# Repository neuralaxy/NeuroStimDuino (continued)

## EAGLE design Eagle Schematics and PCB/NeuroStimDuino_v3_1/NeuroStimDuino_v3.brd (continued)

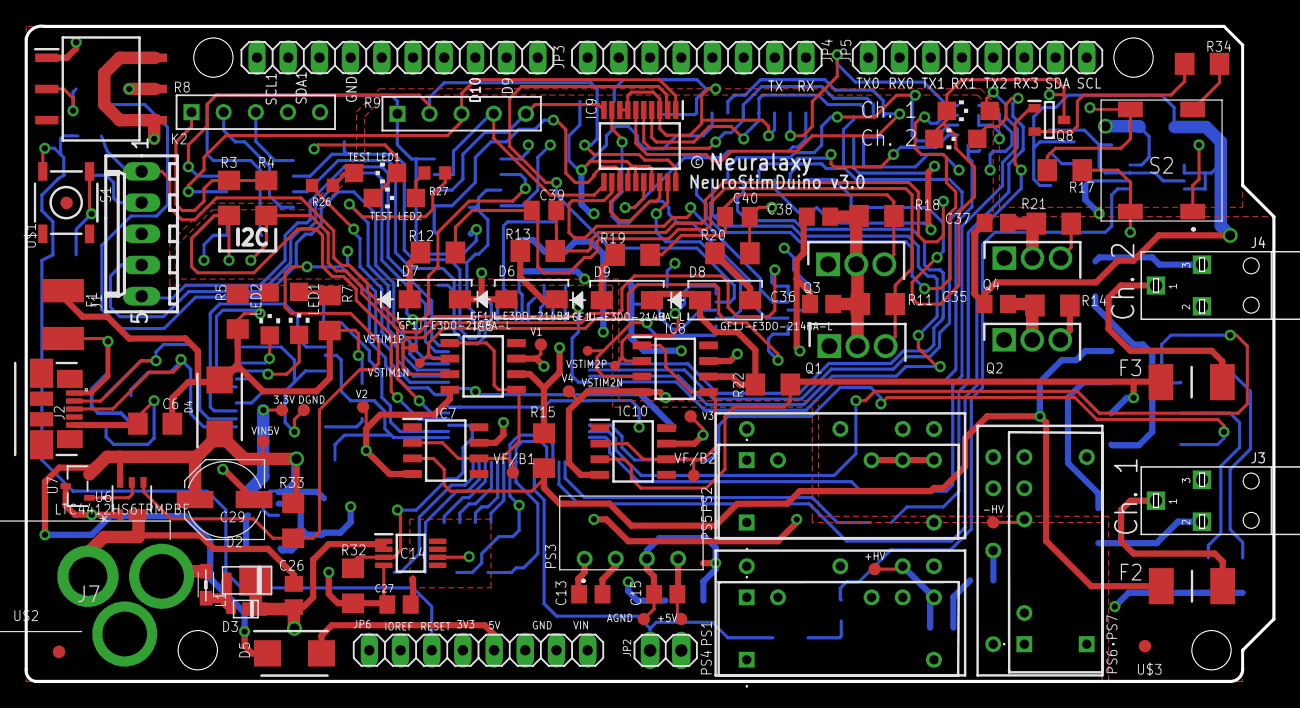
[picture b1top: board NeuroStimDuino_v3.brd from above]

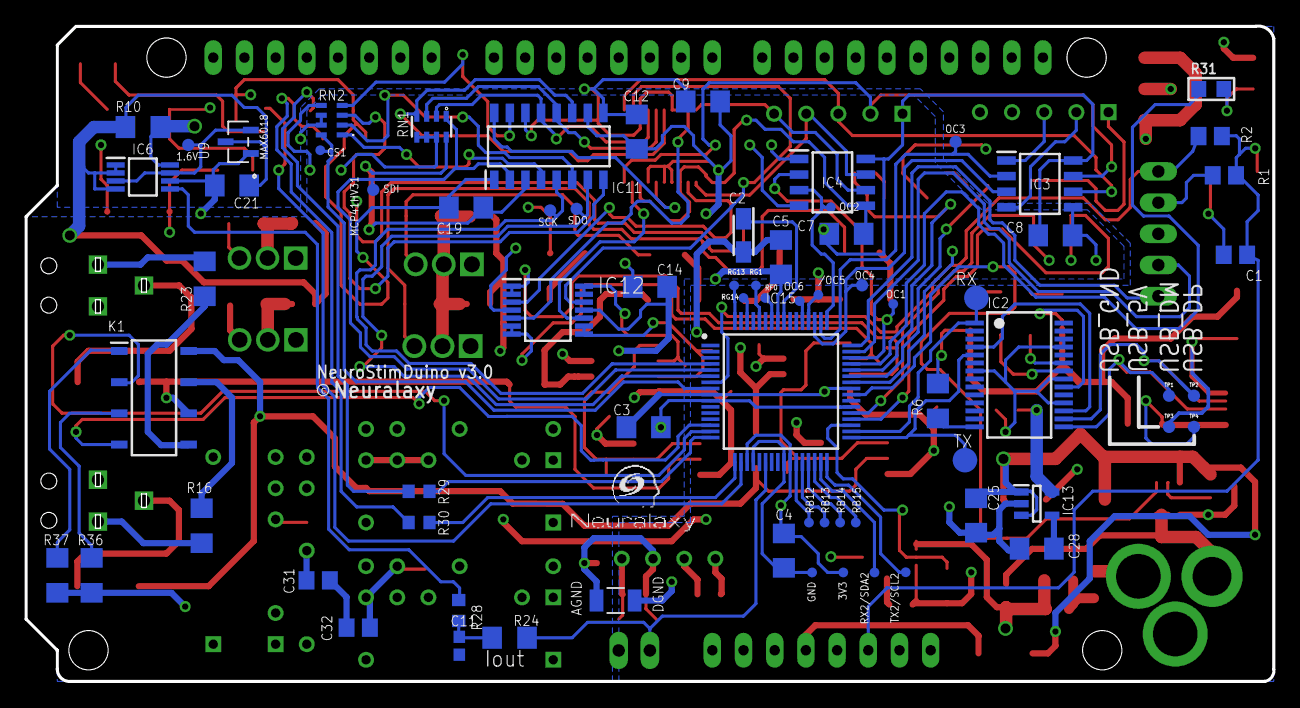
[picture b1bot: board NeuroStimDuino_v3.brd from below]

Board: 4 copper layers, 101.6 x 53.4 mm, 177 parts (68 on the bottom side), 125 nets.

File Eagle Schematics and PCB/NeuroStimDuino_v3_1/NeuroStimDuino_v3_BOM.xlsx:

Qty | Value | Device | Package | Parts | Description | Column1 | _1
3 | 0.1uF | CGA4J2X7R2A104K125AA | C0805K | C1, C39, C40 | CAPACITOR, American symbol
1 | 56nF | C0603C563J4RACTU | CAPC17595_87N_KEM | C11
9 | 1uF | C0805C105K3RACTU | C0805 | C13, C15, C26, C31, C32, C35, C36, C37, C38 | CAPACITOR, American symbol
1 | 4.7uF | F971C475MAAHT3 | CAPPM3216X180N | C2 | Tantalum Capacitors - Solid SMD 16V 4.7uF 20% 1206 ESR=4Ohm AEC-Q200
1 | 10uF | C2012X7S1E106K125AE | C0805 | C27 | CAPACITOR, American symbol
1 | 47uF | 865230445005 | Wurth Electronik | C29 | 47uF
11 | 0.1uF | C1206C104K3RACTU | C1206 | C3, C4, C5, C7, C8, C9, C12, C14, C19, C21, C25 | CAPACITOR, American symbol
2 | 10nF | CGA5H4X7R2J103K115AA | C1206 | C6, C28 | CAPACITOR, American symbol
1 | SS1P3L | 0025_SS1P3L-M3/84A | DO220AAL | D2 | 1A 30V Schottky Barrier Rectifiers -SS1P3L-M3/84A
1 | MSS1P3L-M3/89A | 1653_MSS1P3L-M3/89A | MICROSMP | D3 | Surface Mount Schottky Barrier Rectifiers - Case microSMP
2 | LSM115JE3_TR13 | LSM115JE3_TR13 | DIOM5436X330N | D4, D5 | Schottky Diodes & Rectifiers Schottky
4 | GF1J-E3DO-214BA-L | GF1J-E3DO-214BA-L | DO-214BA-L | D6, D7, D8, D9
2 | 0453.062MR | 0453.062MR | FUSC6127X294N | F2, F3 | Surface Mount Fuses 125VAC 0.062A 5.5ohms 453 NANO2
1 | ACSL-6410-00TE | ACSL-6410-00TE | SOIC127P599X152-16N | IC11 | Broadcom ACSL-6410-00TE DC Input Logic Gate Output Quad Optocoupler, Surface Mo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
1 | MCP6479-E_ST or TS274IPT | MCP6479-E_ST or TS274IPT | SOP65P640X120-14N | IC12 | Operational Amplifiers - Op Amps Quad, 3MHz Op Amp, E Temp
1 | TPS73633DBVR | TPS73633DBVR | SOT95P280X145-5N | IC13 | Single Output LDO, 400mA, Adj.(1.2 to 5.5V), Cap free, Low Noise, Reverse Curre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
1 | MIC3975-5.0YMM-TR | MIC3975-5.0YMM-TR | SOP65P490X109-8N | IC14 | ic
1 | DSPIC33FJ64GS606-I_PT | DSPIC33FJ64GS606-I_PT | QFP50P1200X1200X120-64N | IC15 | Microchip DSPIC33FJ64GS606-I/PT, 16bit PIC Microcontroller, 40MHz, 64 kB Flash,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
2 | HCPL0531 | HCPL0531 | SOIC127P594X363-8N | IC3, IC4 | Optocoupler 2-Ch Transistor 1MBit/s SO8
2 | AD629ARZ-R7 or INA149AID | AD629ARZ-R7 or INA149AID | SOIC127P600X175-8N | IC5, IC8 | Texas Instruments INA149AID, Differential Amplifier 8-Pin SOIC
1 | TSC2012IST | TSC2012IST | SOP65P490X110-8N | IC6 | SP Amp Current Sense Amp Single 5.5V 8-Pin Mini-SO T/R
2 | OPA140AID | OPA140AID | SOIC127P600X175-8N | IC7, IC10 | 11MHz, Single Supply, Low Noise, Precision, Rail-to-Rail Output, JFET Amplifier
1 | MCP4341-103E_ST | MCP4341-103E_ST | SOP65P640X120-20N | IC9 | 7 bit Digital Potentiometers, 10k, SPI
1 | 22-27-2051-05 | 22-27-2051-05 | 6410-05 | J1 | CONNECTOR
2 | Custom Connector | DC_JACK_081BB-2103300 | 081BB-2103300 | J3, J4
1 | CON-SOCJ-2155 | CON-SOCJ-2155 | CONSOCJ2155 | J7 | DC Power Connectors Power Jack/Connector 2.1mm x 5.5mm
1 | Stackable Header - 2 Pin |  | 1X02 | JP2 | Female Gray Connecter strip 2x1 F V h 8,5 p2,54mm
1 | Stackable Header - 10 Pin | https://robu.in/product/10-pin-female-11mm-tall-stackable-he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 | 1X10 | JP3 | Female Gray Connector strip for Arduino 3V3 bases - 10x1 F V h 8,5 p2,54mm
3 | Stackable Header - 8 Pin | https://robu.in/product/8-pin-female-11mm-tall-stackable-hea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 | 1X08 | JP4, JP5, JP6 | Female Gray Connector strip for Arduino 3V3 bases - 8x1 F V h 8,5 p2,54mm
1 | CPC2125N | CPC2125N | SOP254P610X218-8N | K1 | Solid State Relays - PCB Mount Dual SP-NC SS OptoMOS Relay
1 | LCA717S_DC | LCA717S_DC | SOP254P952X470-6N | K2 | Solid State Relays - PCB Mount 1-Form 30V 2000 mA Solid State Relay
1 | BLM21PG300SN1D | BLM21PG300SN1D | 0805 | L1 | BLM21
4 | LED | APTR3216SGC | CHIPLED_1206 | LED5, LED6, LED7, LED8 | LED
2 | IH0524D or IH0524SH | IH0524D or IH0524SH | IH0524D or IH0524SH | PS4, PS6 or PS1, PS7 | Isolated DC/DC Converters DC-DC, 2W, unreg., dual output, SIP, 3kV
1 | TEA_1-0505 | TEA_1-0505 | TEA10505 | PS3 | 1 Watt DC/DC converter, industrial, +/-10% input, unregulated, highly cost effi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
2 | MJE350 | MJE350 | TO229P300X760X1364-3P | Q1, Q3 | Source: Datasheet
2 | MJE340 | MJE340 | TO229P290X760X1320-3P | Q2, Q4 | MJE340, NPN Bipolar Transistor, 0.5 A 300 V HFE:30 V Power, 3-Pin SOT-32
1 | MMBT3906 | MMBT3906 | SOT95P240X120-3N | Q8 | Transistor GP BJT PNP 40V 0.2A SOT23 Fairchild MMBT3906 PNP Bipolar Transistor,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
1 | 10K | RC0805FR-0710KL | R0805 | R1 | RESISTOR, American symbol
1 | 0.5E | RCWE1206R500FKEA | R1206 | R10 | RESISTOR, American symbol
4 | 35.7K | RT1206FRE0735K7L | R1206 | R11, R14, R18, R21 | RESISTOR, American symbol
4 | 10K, 1/2W | RCS120610K0JNEA | R1206 | R12, R13, R19, R20 | RESISTOR, American symbol
2 | 100E, 1/2W | MCA1206MD1000BP100 | R1206 | R15, R22 | RESISTOR, American symbol
2 | 10E, 3/4W | CRCW120610R0FKEBHP | R1206 | R16, R23 | RESISTOR, American symbol
1 | 3.3K | ERJ-8ENF3301V | R1206 | R17 | RESISTOR, American symbol
1 | 470E | ERJ-8ENF4700V | R0805 | R2 | RESISTOR, American symbol
5 | 330E | ERJ-UP3J331V | R0603 | R26, R27, R28, R29, R30 | RESISTOR, American symbol
2 | 10K | CRGH1206F10K | R1206 | R3, R4 | RESISTOR, American symbol
1 | 100E | R_0805 | R0805 | R31 | RESISTOR
1 | 100K | ERJ-UP8F1003V | R1206 | R32 | RESISTOR, American symbol
1 | 470K | ERJ-UP8F4703V | R1206 | R33 | RESISTOR, American symbol
1 | 220E | ERJ-8ENF2200V | R1206 | R34 | RESISTOR, American symbol
2 | 330E | R-US_R1206 | R1206 | R36, R37 | RESISTOR, American symbol
1 | 4605X-101-221LF | 4605X-101-221LF | BO_4605X | R8
1 | 4605X-101-332LF | 4605X-101-332LF | BO_4605X | R9
1 | CAY16-332J4LF | CAY16-332J4LF | CAY16-J4 | RN1 | Bourns CAY16 Series 3.3k +/-5% Isolated SMT Resistor Array, 4 Resistors, 0.25W 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
1 | CAY16-181J4LF | CAY16-181J4LF | CAY16181J4LF | RN2 | BOURNS - CAY16-181J4LF - Fixed Network Resistor, 180 ohm, Isolated, 4 Elements,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
1 | PTS525SM15SMTR2 LFS | PTS525SM15SMTR2 LFS | TACTILE_SWITCH_SMD | S1
1 | 3006.2115 or 3006.2101 | 3006.2115 or 3006.2101 | 30062115 | S2 | Tactile Switches TACTILE
1 | LTC4412HS6TRMPBF | LTC4412HS6TRMPBF | TSOT-23_S6_ADI | U6
1 | PMV48XP,215 | PMV48XP,215 | TO-236_SOT23_NEX-L | U7
1 | MAX6018BEUR16+T | MAX6018BEUR16+T | 21-0051H_MXM | U9
114 |  |  |  |  |  |  | 62

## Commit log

2021-03-12 NeuroStimDuino v1.0 schematic and PCB
2021-04-06 Initial Commit for NeuroStimDuino Library
2021-04-06 Rename Software/Readme.md to Software/NeuroStimDuino/Readme.md
2021-04-06 Added copy of CNU License
2021-04-21 Sample stimulation current using on-board sensor
2021-04-28 Updated changeI2Caddress_Callback() to add progam/switch_only flag
2021-06-01 NeuroStimDuino_v1.1 schematic and PCB files
2021-06-26 Uploading gerber files for NeuroStimDuino v1.1
2021-10-04 hex file for PIC controller on-board NeuroStimDuino
    1. Foe these steps for loading a pre-built hex file, without compiling the source code: https://www.youtube.com/watch?v=pEMORwwuyos
    2. Select microcontroller as dsPIC33FJ256GP506A
2021-10-13 Added instructions fro accessing the source code
2021-10-13 Added details for accessing source code
2021-10-13 Read current sensor and register values using I2C
2021-10-30 Update description of instructions
2021-11-01 Added current_conversion_ratio and routine house keeping
2021-11-01 Added get started tutorial
2021-11-01 Added links
2021-11-01 Added details about jumper and switch settings
2021-11-15 Allows user to input floating point current amplitude via "AMPL" command
2021-11-18 Updated Welcome message
2021-11-18 Convert READ output to float for AMPL register
    Added delay of 3ms after I2C Write() and before I2C Read(), to allow dsPIC sufficient time to process the write instruction
2021-11-27 Updated neuromuscular stimulation demo video
2021-12-07 Add BOM and pick n place files
2023-01-04 Create NeuroStimDuino v1.0 Getting Started
2023-01-21 Added pin diagram and layout for NSDuino2.1
2023-01-23 Add RAMP command, increase current limit to 31mA
2023-01-23 Added Ramping Command
2023-01-23 Added board layout and pinout
2023-02-08 Add more details to Software Setup section
2023-03-30 Added Gerber files for NeuroStimDuino_v2.1
2023-03-30 Eagle files of NSDuino v1.1
2023-03-30 Eagle files for NSDuino_v2.1
2024-09-11 Create v2.1 folder
2024-09-11 Add HEX file for v2.1 board
2024-09-11 Create v1.0 folder
2025-10-01 Update README.md
    Launch of NSDuino 3.0
2026-03-12 Added NeuroStimDuino v3.1 EAGLE schematics+PCB
2026-03-12 Corrected version number to 3.0 instead of 3.1
